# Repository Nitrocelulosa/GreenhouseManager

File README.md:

# GreenhouseManager
Es el proyecto de fin de semestre para ELO de la USM

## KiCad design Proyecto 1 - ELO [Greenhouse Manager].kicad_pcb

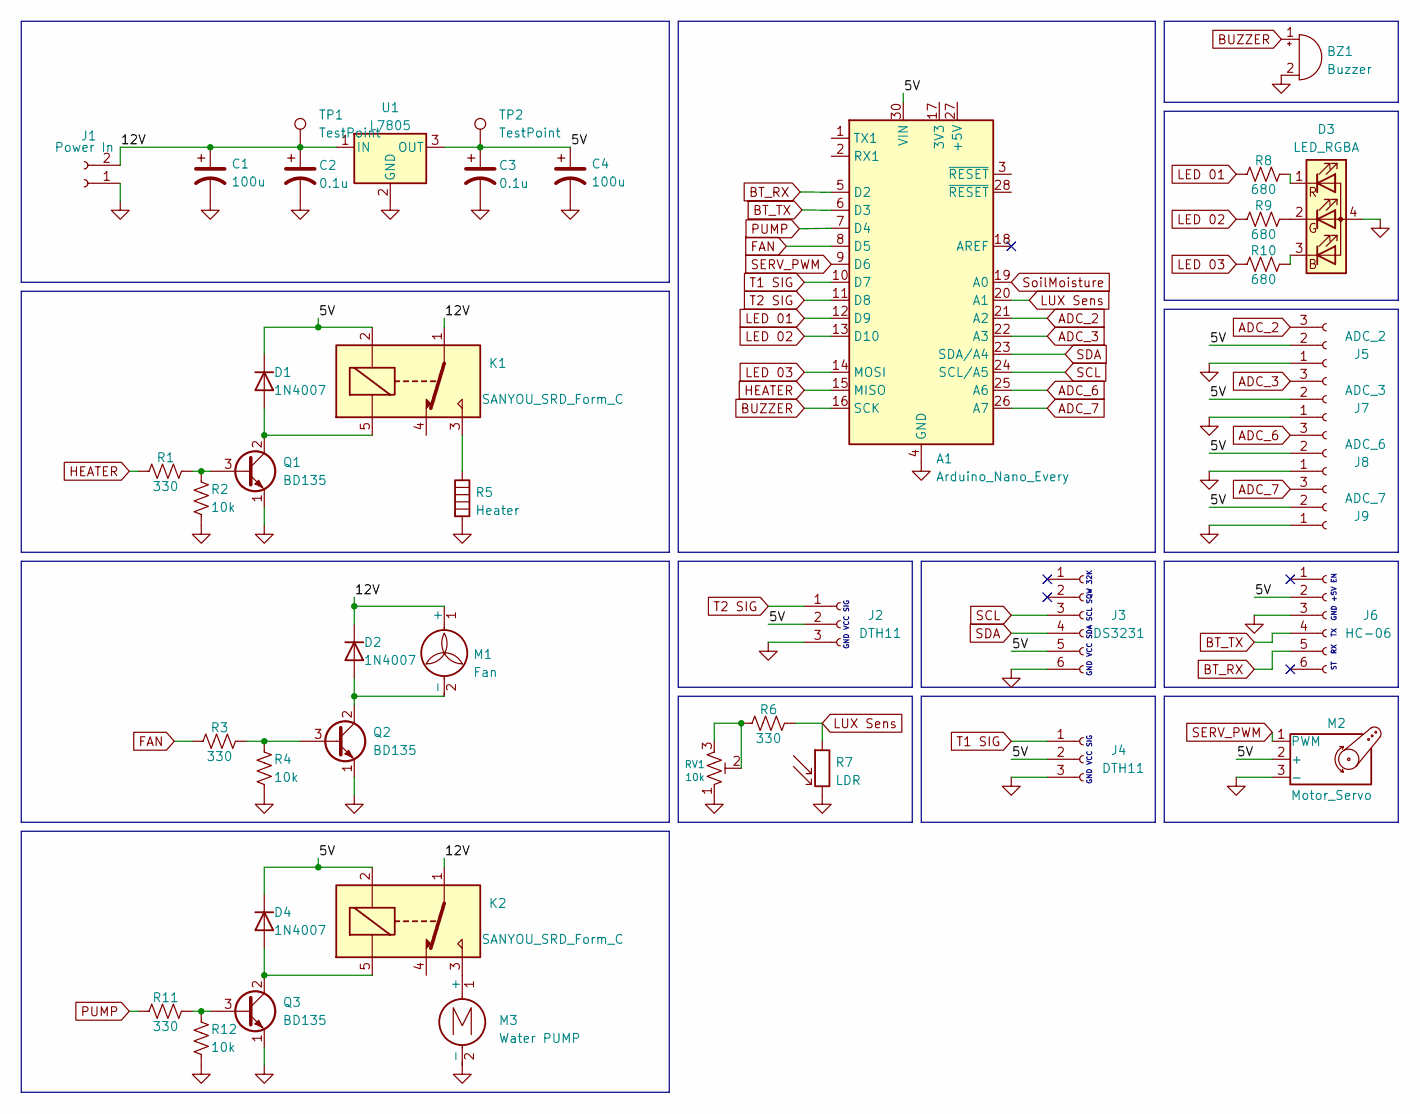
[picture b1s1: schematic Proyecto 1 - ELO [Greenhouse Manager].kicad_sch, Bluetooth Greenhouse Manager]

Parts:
A1: Arduino_Nano_Every; Arduino_Nano
BZ1: Buzzer; Buzzer_12x9.5RM7.6
C1, C4: 100u; CP_Radial_D7.5mm_P2.50mm
C2, C3: 0.1u; CP_Radial_D7.5mm_P2.50mm
D1, D2, D4: 1N4007; D_DO-41_SOD81_P10.16mm_Horizontal
D3: LED_RGBA; LED_Cree-PLCC4_3.2x2.8mm_CCW
J1: Power In; TerminalBlock_Phoenix_MKDS-1,5-2-5.08_1x02_P5.08mm_Horizont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
J2, J4: DTH11; PinHeader_1x03_P2.54mm_Vertical
J3: DS3231; PinSocket_1x06_P2.54mm_Vertical
J5: ADC_2; PinHeader_1x03_P2.54mm_Vertical
J6: HC-06; PinSocket_1x06_P2.54mm_Vertical
J7: ADC_3; PinHeader_1x03_P2.54mm_Vertical
J8: ADC_6; PinHeader_1x03_P2.54mm_Vertical
J9: ADC_7; PinHeader_1x03_P2.54mm_Vertical
K1, K2: SANYOU_SRD_Form_C; Relay_SPDT_SANYOU_SRD_Series_Form_C
M1: Fan; Molex_KK-254_AE-6410-02A_1x02_P2.54mm_Vertical
M2: Motor_Servo; PinHeader_1x03_P2.54mm_Vertical
M3: Water PUMP; TerminalBlock_Phoenix_MKDS-1,5-2-5.08_1x02_P5.08mm_Horizont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
Q1, Q2, Q3: BD135; TO-126-3_Vertical
R1, R3, R6, R11: 330; R_Axial_DIN0204_L3.6mm_D1.6mm_P5.08mm_Horizontal
R2, R4, R12: 10k; R_Axial_DIN0204_L3.6mm_D1.6mm_P5.08mm_Horizontal
R5: Heater; TerminalBlock_Phoenix_MKDS-1,5-2-5.08_1x02_P5.08mm_Horizont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
R7: LDR; PinSocket_1x02_P2.54mm_Vertical
R8, R9, R10: 680; R_0805_2012Metric
RV1: 10k; PinHeader_1x03_P2.54mm_Vertical
TP1, TP2: TestPoint; Pin_D0.7mm_L6.5mm_W1.8mm_FlatFork
U1: L7805; TO-220-3_Vertical

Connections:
/5V: A1.30 (VIN), C3.1, C4.1, D1.1 (K), D4.1 (K), J2.2, J3.5, J4.2, J5.2, J6.2, J7.2, J8.2, J9.2, K1.2, K2.2, M2.2 (+), TP2.1, U1.3 (OUT)
/12V: C1.1, C2.1, D2.1 (K), J1.2, K1.1, K2.1, M1.1 (+), TP1.1, U1.1 (IN)
ADC_2: A1.21 (A2), J5.3
ADC_3: A1.22 (A3), J7.3
ADC_6: A1.25 (A6), J8.3
ADC_7: A1.26 (A7), J9.3
BT_RX: A1.5 (D2), J6.5
BT_TX: A1.6 (D3), J6.4
BUZZER: A1.16 (SCK), BZ1.1 (-)
FAN: A1.8 (D5), R3.1
GND: A1.4 (GND), A1.29 (GND), BZ1.2 (+), C1.2, C2.2, C3.2, C4.2, D3.4 (A), J1.1, J2.3, J3.6, J4.3, J5.1, J6.3, J7.1, J8.1, J9.1, M2.3 (-), M3.2 (-), Q1.1 (E), Q2.1 (E), Q3.1 (E), R2.2, R4.2, R5.2, R7.2, R12.2, RV1.1, U1.2 (GND)
HEATER: A1.15 (MISO), R1.1
LED 01: A1.12 (D9), R8.1
LED 02: A1.13 (D10), R9.1
LED 03: A1.14 (MOSI), R10.1
LUX Sens: A1.20 (A1), R6.2, R7.1
unnamed: D1.2 (A), K1.5, Q1.2 (C)
unnamed: D2.2 (A), M1.2 (-), Q2.2 (C)
unnamed: D3.1 (RK), R8.2
unnamed: D3.2 (GK), R9.2
unnamed: D3.3 (BK), R10.2
unnamed: D4.2 (A), K2.5, Q3.2 (C)
unnamed: K1.3, R5.1
unnamed: K2.3, M3.1 (+)
unnamed: Q1.3 (B), R1.2, R2.1
unnamed: Q2.3 (B), R3.2, R4.1
unnamed: Q3.3 (B), R11.2, R12.1
unnamed: R6.1, RV1.2, RV1.3
PUMP: A1.7 (D4), R11.1
SCL: A1.24 (SCL/A5), J3.3
SDA: A1.23 (SDA/A4), J3.4
SERV_PWM: A1.9 (D6), M2.1 (PWM)
SoilMoisture: A1.19 (A0)
T1 SIG: A1.10 (D7), J4.1
T2 SIG: A1.11 (D8), J2.1

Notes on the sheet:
GND VCC SIG
GND VCC SDA SCL SQW 32K
ST RX TX GND +5V EN

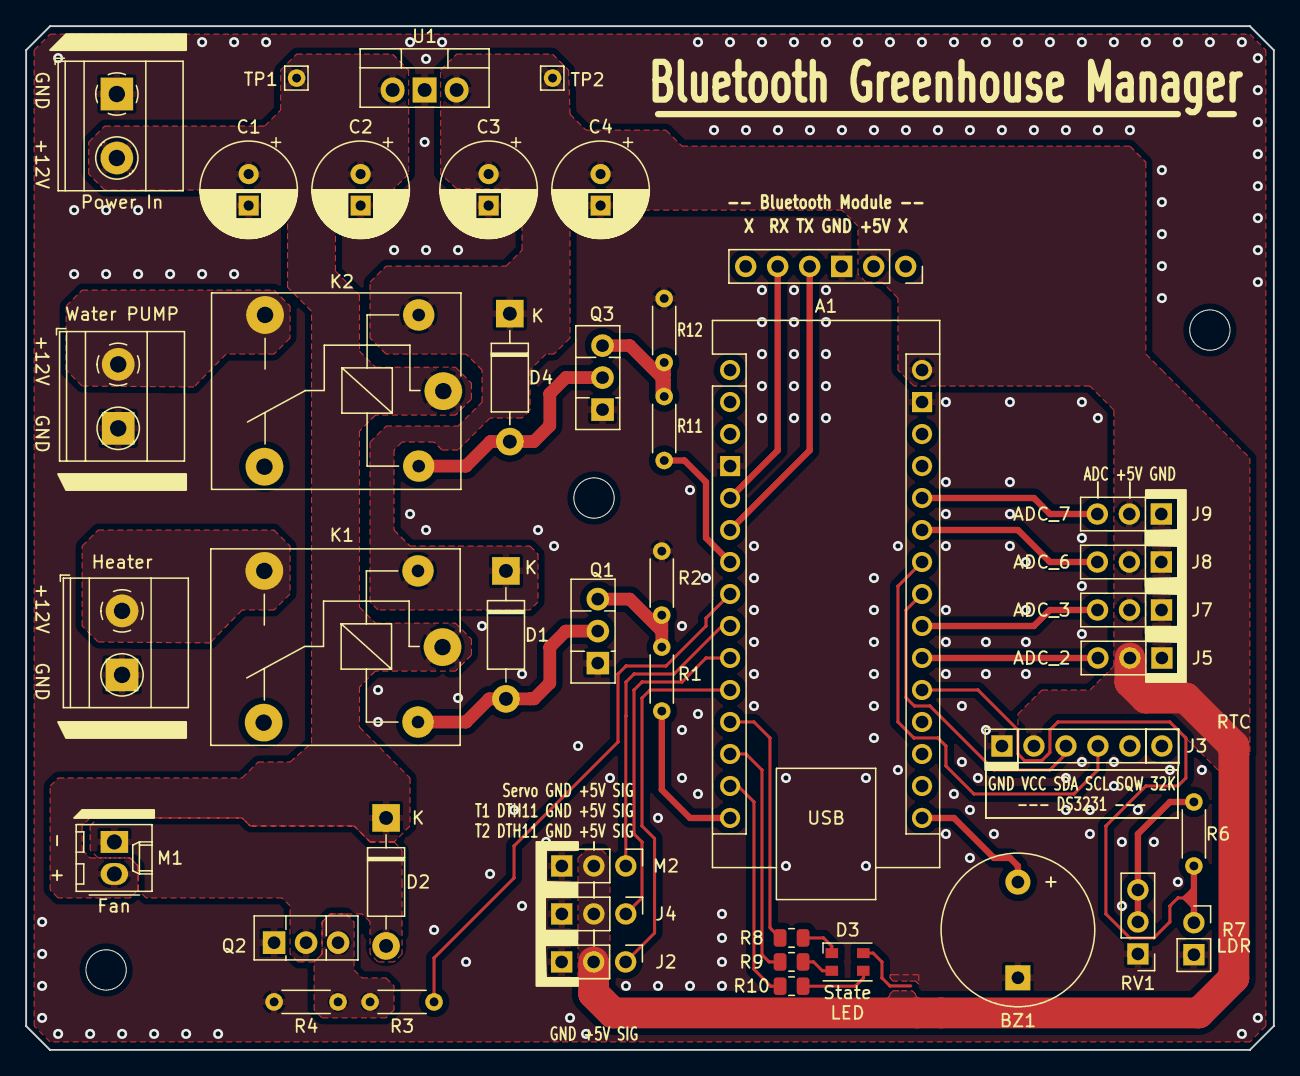
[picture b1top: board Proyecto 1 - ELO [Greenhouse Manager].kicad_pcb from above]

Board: 2 copper layers, 99.1 x 81.3 mm, 44 parts (0 on the bottom side), 34 nets.

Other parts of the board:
Agujero: MountingHole_3.2mm_M3

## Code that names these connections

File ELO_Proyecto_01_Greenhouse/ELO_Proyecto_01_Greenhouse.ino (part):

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#include <Servo.h>

// PINES Digitales
const char bt_rx     =  2;
const char bt_tx     =  3;
const char pump      =  4;
const char fan       =  5;
const char servo_pin =  6;
const char t_sen_1   =  7;
const char t_sen_2   =  8;
const char LED01     =  9;
const char LED02     = 10;
const char LED03     = 11;
const char HEATER    = 12;
const char BUZZER    = 13;

// PINES Analogos (Equivalencias con el esquema)
//const char SoilMoisture = 14;  // A0
const char LUX_Sens     = 15;  // A1
const char ADC_2        = 16;  // A2
const char ADC_3        = 17;  // A3
const char ADC_6        = 20;  // A6
//const char ADC_7        = 21;  // A7
const char SoilMoisture = 21;  // A7 debido a un error de diseño en la palca

// Cosas constantes
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  servo.attach(servo_pin);

  // Se declaran como salidas/entradas digitales los siguientes pines
  pinMode(pump  , 1);
  pinMode(fan   , 1);
  pinMode(LED01 , 1);
  pinMode(LED02 , 1);
  pinMode(LED03 , 1);
  pinMode(HEATER, 1);
  pinMode(BUZZER, 1);
  digitalWrite(LED01,1);
  digitalWrite(LED02,1);
  digitalWrite(LED03,0);
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
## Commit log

2023-06-02 Update 1
2023-06-12 Update ELO_Proyecto_01_Greenhouse.ino
    ufffffffffffffffffff
2023-06-12 Update ELO_Proyecto_01_Greenhouse.ino
    Toy en la biblioteca re aburridoooooooooooo
2023-06-12 Update ELO_Proyecto_01_Greenhouse.ino
    Yeah, a comer
2023-06-26 Update ELO_Proyecto_01_Greenhouse.ino
    Yep, this is laaaaarge
